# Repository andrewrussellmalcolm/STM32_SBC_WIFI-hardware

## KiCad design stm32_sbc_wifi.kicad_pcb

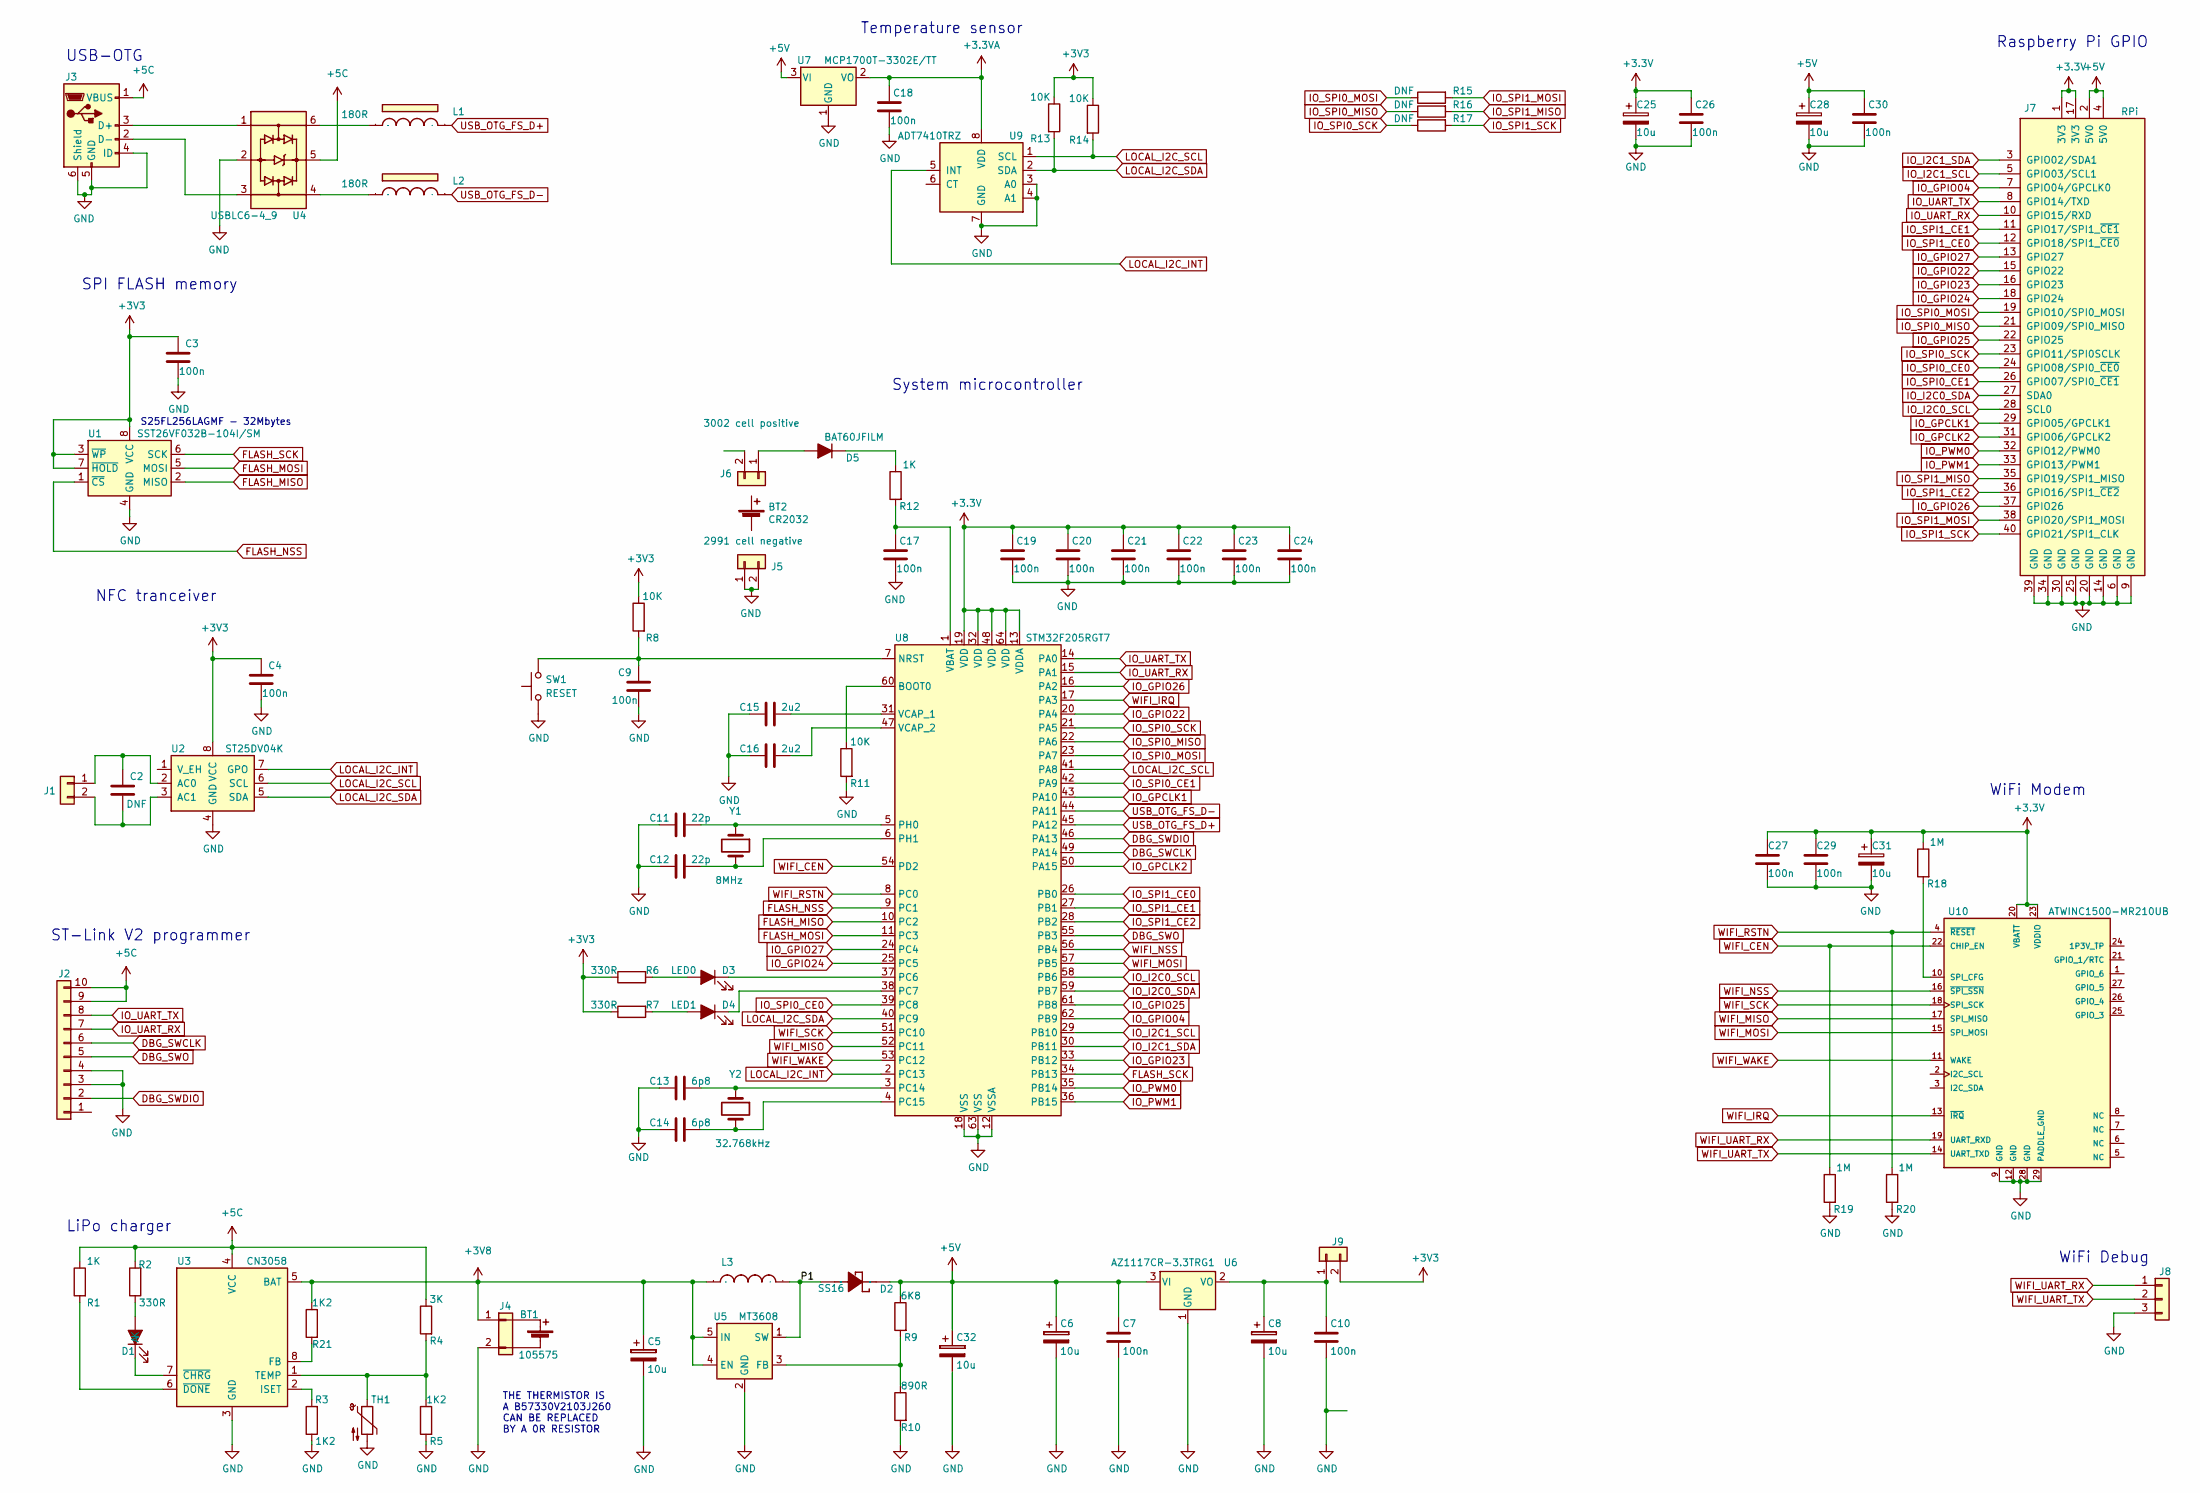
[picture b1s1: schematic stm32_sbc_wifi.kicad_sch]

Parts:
BT1: 105575; 103040_5000mAh_LiPo; Voltage 3; PartNo 97384022
BT2: CR2032; dummy
C2: DNF; C_0603_1608Metric
C3, C7, C9, C10, C17, C19, C20, C21, C22, C23, C24, C26, C30: 100n; C_0603_1608Metric; PartNo C0603C104K3RACTU
C4, C18: 100n; C_0603_1608Metric; Voltage 50V; PartNo C0603C104K4RACTU
C5, C6, C8, C32: 10u; CP_EIA-3216-10_Kemet-I; PartNo TAJR106K006RNJ
C11, C12: 22p; C_0603_1608Metric; PartNo C0603C220J5GACTU
C13, C14: 6p8; C_0603_1608Metric; PartNo C0603C689C5GACTU
C15, C16: 2u2; C_0603_1608Metric; PartNo C0603C225K4PACTU
C25, C28: 10u; CP_EIA-3216-10_Kemet-I
C27, C29: 100n; C_0603_1608Metric; Voltage 50V; PartNo C0603C104K3RACTU
C31: 10u; CP_EIA-3216-10_Kemet-I; Voltage 6.3V; PartNo TAJR106K006RNJ
D1: LTST-C190KRKT; 3mm_right_angle_LED
D2: SS16; SM_DIODE_DO214AC_1; PartNo SS16
D3: LED0; 3mm_right_angle_LED; PartNo LS Q976
D4: LED1; 3mm_right_angle_LED; PartNo LB Q39E-L2OO-35-1
D5: BAT60JFILM; D_SOD-323; PartNo BAT60JFILM
J1: Conn_01x02; Molex_PicoBlade_53047-0210_1x02_P1.25mm_Vertical; PartNo 53047-0210
J2: Conn_01x10; IDC-Header_2x05_P2.54mm_Vertical; PartNo T821110A1S100CEU
J3: USB_OTG; USB_Micro-B_Molex-105017-0001; PartNo 105017-0001
J4: Conn_01x02; JST_PH_B2B-PH-K_1x02_P2.00mm_Vertical
J5: 2991 cell negative; SM_BATTERY_2991_(KEYSTONE)_1; PartNo 2991TR
J6: 3002 cell positive; SM_BATTERY_3002_(KEYSTONE)_1; PartNo 3002TR
J7: RPi; PinHeader_2x20_P2.54mm_Vertical
J8: Conn_01x03; Molex_KK-254_AE-6410-03A_1x03_P2.54mm_Vertical; PartNo 22-27-2031
J9: Conn_01x02; PinHeader_1x02_P2.54mm_Horizontal
L1, L2: 180R; L_0603_1608Metric; PartNo 742792624
L3: L_10.4x10.4_H4.8; PartNo SRN5020-150M; Farnell not FEC, RS 749-8653
R1, R12: 1K; R_0603_1608Metric; PartNo CRG0603F1K
R2: 330R; R_0603_1608Metric
R3: 1K2; R_0603_1608Metric
R4: 3K; R_0603_1608Metric; PartNo CRG0603F1K
R5, R21: 1K2; R_0603_1608Metric; PartNo CRG0603F1K
R6, R7: 330R; R_0603_1608Metric; PartNo CRG0603F330R
R8, R11: 10K; R_0603_1608Metric; PartNo CRG0603F10K
R9: 6K8; R_0603_1608Metric; PartNo CRG0603F1K
R10: 890R; R_0603_1608Metric; PartNo CRG0603F1K
R13, R14: 10K; R_0603_1608Metric; PartNo CRG0603F2K2
R15, R16, R17: DNF; R_0603_1608Metric; PartNo CRG0603F330R
R18, R19, R20: 1M; R_0603_1608Metric; PartNo CRG0603F10K
SW1: RESET; SW_SPST_B3S-1000
TH1: B57330V2103J260; R_0603_1608Metric
U1: SST26VF032B-104I/SM; SOIC-8W_5.3x5.3mm_P1.27mm; PartNo SST26VF032B-104I/SM
U2: ST25DV04K; SOIC-8_3.9x4.9mm_P1.27mm; PartNo ST25DV04K
U3: CN3058; SOIC-8-1EP_3.9x4.9mm_P1.27mm_EP2.29x3mm
U4: USBLC6-4_9; SOT-23-6; PartNo USBLC6-2SC6Y
U5: MT3608; SOT-23-6
U6: AZ1117CR-3.3TRG1; SOT-89-3; PartNo AZ1117CR-3.3TRG1
U7: MCP1700T-3302E/TT; SOT-23
U8: STM32F205RGT7; LQFP-64_10x10mm_P0.5mm; PartNo STM32F205RGT7
U9: ADT7410TRZ; SOIC-8_3.9x4.9mm_P1.27mm; PartNo HTS221TR
U10: ATWINC1500-MR210UB; MICROCHIP_ATWINC1500-MR210UB
Y1: 8MHz; Crystal_SMD_5032-2Pin_5.0x3.2mm; PartNo 144-5033
Y2: 32.768kHz; Crystal_SMD_2012-2Pin_2.0x1.2mm; PartNo 144-2324

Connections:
+3.3VA: C18.2, U7.2 (VO), U9.8 (VDD)
+3V8: C5.1, J4.1, L3.1, R21.1, U3.5 (BAT), U5.4 (EN), U5.5 (IN)
+5C: J2.9, J2.10, J3.1 (VBUS), R1.1, R2.2, R4.1, U3.4 (VCC), U4.5
+5V: C6.1, C7.1, C28.1, C30.2, C32.1, D2.1 (ANODE), J7.2 (5V0), J7.4 (5V0), R9.1, U6.3 (VI), U7.3 (VI)
/P1: D2.2 (CATHODE), L3.2, U5.1 (SW)
DBG_SWCLK: J2.6, U8.49 (PA14)
DBG_SWDIO: J2.2, U8.46 (PA13)
DBG_SWO: J2.5, U8.55 (PB3)
FLASH_MISO: U1.2 (MISO), U8.10 (PC2)
FLASH_MOSI: U1.5 (MOSI), U8.11 (PC3)
FLASH_NSS: U1.1 (~CS), U8.9 (PC1)
FLASH_SCK: U1.6 (SCK), U8.34 (PB13)
GND: C3.1, C4.1, C5.2, C6.2, C7.2, C8.2, C9.1, C10.2, C11.2, C12.2, C13.2, C14.2, C15.2, C16.2, C17.1, C18.1, C19.1, C20.1, C21.1, C22.1, C23.1, C24.1, C25.2, C26.1, C27.2, C28.2, C29.2, C30.1, C31.2, C32.2, J2.3, J2.4, J3.4 (ID), J3.5 (GND), J3.6 (Shield), J4.2, J5.1, J5.2, J7.6 (GND), J7.9 (GND), J7.14 (GND), J7.20 (GND), J7.25 (GND), J7.30 (GND), J7.34 (GND), J7.39 (GND), J8.3, R3.1, R5.2, R10.2, R11.2, R19.2, R20.2, SW1.1, TH1.2, U1.4 (GND), U2.4 (GND), U3.3 (GND), U4.2, U5.2 (GND), U6.1 (GND), U7.1 (GND), U8.12 (VSSA), U8.18 (VSS), U8.63 (VSS), U9.3 (A0), U9.4 (A1), U9.7 (GND), U10.9 (GND), U10.12 (GND), U10.28 (GND), U10.29 (PADDLE_GND)
IO_GPCLK1: J7.29 (GPIO05/GPCLK1), U8.43 (PA10)
IO_GPCLK2: J7.31 (GPIO06/GPCLK2), U8.50 (PA15)
IO_GPIO04: J7.7 (GPIO04/GPCLK0), U8.62 (PB9)
IO_GPIO22: J7.15 (GPIO22), U8.20 (PA4)
IO_GPIO23: J7.16 (GPIO23), U8.33 (PB12)
IO_GPIO24: J7.18 (GPIO24), U8.25 (PC5)
IO_GPIO25: J7.22 (GPIO25), U8.61 (PB8)
IO_GPIO26: J7.37 (GPIO26), U8.16 (PA2)
IO_GPIO27: J7.13 (GPIO27), U8.24 (PC4)
IO_I2C0_SCL: J7.28 (SCL0), U8.58 (PB6)
IO_I2C0_SDA: J7.27 (SDA0), U8.59 (PB7)
IO_I2C1_SCL: J7.5 (GPIO03/SCL1), U8.29 (PB10)
IO_I2C1_SDA: J7.3 (GPIO02/SDA1), U8.30 (PB11)
IO_PWM0: J7.32 (GPIO12/PWM0), U8.35 (PB14)
IO_PWM1: J7.33 (GPIO13/PWM1), U8.36 (PB15)
IO_SPI0_CE0: J7.24 (GPIO08/SPI0_~CE0), U8.39 (PC8)
IO_SPI0_CE1: J7.26 (GPIO07/SPI0_~CE1), U8.42 (PA9)
IO_SPI0_MISO: J7.21 (GPIO09/SPI0_MISO), R16.1, U8.22 (PA6)
IO_SPI0_MOSI: J7.19 (GPIO10/SPI0_MOSI), R15.1, U8.23 (PA7)
IO_SPI0_SCK: J7.23 (GPIO11/SPI0SCLK), R17.1, U8.21 (PA5)
IO_SPI1_CE0: J7.12 (GPIO18/SPI1_~CE0), U8.26 (PB0)
IO_SPI1_CE1: J7.11 (GPIO17/SPI1_~CE1), U8.27 (PB1)
IO_SPI1_CE2: J7.36 (GPIO16/SPI1_~CE2), U8.28 (PB2)
IO_SPI1_MISO: J7.35 (GPIO19/SPI1_MISO), R16.2
IO_SPI1_MOSI: J7.38 (GPIO20/SPI1_MOSI), R15.2
IO_SPI1_SCK: J7.40 (GPIO21/SPI1_CLK), R17.2
IO_UART_RX: J2.7, J7.10 (GPIO15/RXD), U8.15 (PA1)
IO_UART_TX: J2.8, J7.8 (GPIO14/TXD), U8.14 (PA0)
LOCAL_I2C_INT: U2.7 (GPO), U8.2 (PC13), U9.5 (INT)
LOCAL_I2C_SCL: R14.2, U2.6 (SCL), U8.41 (PA8), U9.1 (SCL)
LOCAL_I2C_SDA: R13.2, U2.5 (SDA), U8.40 (PC9), U9.2 (SDA)
unnamed: D1.2 (A), R2.1
unnamed: D1.1 (K), U3.7 (~CHRG)
unnamed: D3.2 (A), R6.2
unnamed: D3.1 (K), U8.37 (PC6)
unnamed: D4.2 (A), R7.2
unnamed: D4.1 (K), U8.38 (PC7)
unnamed: D5.2 (A), J6.1
unnamed: D5.1 (K), R12.1
unnamed: C2.2, J1.1, U2.2 (AC0)
unnamed: C2.1, J1.2, U2.3 (AC1)
unnamed: J3.3 (D+), U4.1
unnamed: J3.2 (D-), U4.3
unnamed: C8.1, C10.1, J9.1, U6.2 (VO)
unnamed: L1.1, U4.6
unnamed: L2.1, U4.4
unnamed: R21.2, U3.8 (FB)
unnamed: R3.2, U3.2 (ISET)
unnamed: R4.2, R5.1, TH1.1, U3.1 (TEMP)
unnamed: R1.2, U3.6 (~DONE)
unnamed: R9.2, R10.1, U5.3 (FB)
unnamed: R11.1, U8.60 (BOOT0)
unnamed: C9.2, R8.2, SW1.2, U8.7 (NRST)
unnamed: C13.1, U8.3 (PC14), Y2.1
unnamed: C14.1, U8.4 (PC15), Y2.2
unnamed: C11.1, U8.5 (PH0), Y1.1
unnamed: C12.1, U8.6 (PH1), Y1.2
unnamed: C17.2, R12.2, U8.1 (VBAT)
unnamed: C15.1, U8.31 (VCAP_1)
unnamed: C16.1, U8.47 (VCAP_2)
unnamed: R18.2, U10.10 (SPI_CFG)
USB_OTG_FS_D+: L1.2, U8.45 (PA12)
USB_OTG_FS_D-: L2.2, U8.44 (PA11)
WIFI_CEN: R19.1, U8.54 (PD2), U10.22 (CHIP_EN)
WIFI_IRQ: U8.17 (PA3), U10.13 (~IRQ)
WIFI_MISO: U8.52 (PC11), U10.17 (SPI_MISO)
WIFI_MOSI: U8.57 (PB5), U10.15 (SPI_MOSI)
WIFI_NSS: U8.56 (PB4), U10.16 (~SPI_SSN)
WIFI_RSTN: R20.1, U8.8 (PC0), U10.4 (~RESET)
WIFI_SCK: U8.51 (PC10), U10.18 (SPI_SCK)
WIFI_UART_RX: J8.1, U10.19 (UART_RXD)
WIFI_UART_TX: J8.2, U10.14 (UART_TXD)
WIFI_WAKE: U8.53 (PC12), U10.11 (WAKE)

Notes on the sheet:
LiPo charger
Raspberry Pi GPIO
SPI FLASH memory
WiFi Debug
S25FL256LAGMF - 32Mbytes
THE THERMISTOR IS A B57330V2103J260 CAN BE REPLACED BY A 0R RESISTOR
NFC tranceiver
USB-OTG
System microcontroller
WiFi Modem
ST-Link V2 programmer
Temperature sensor

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
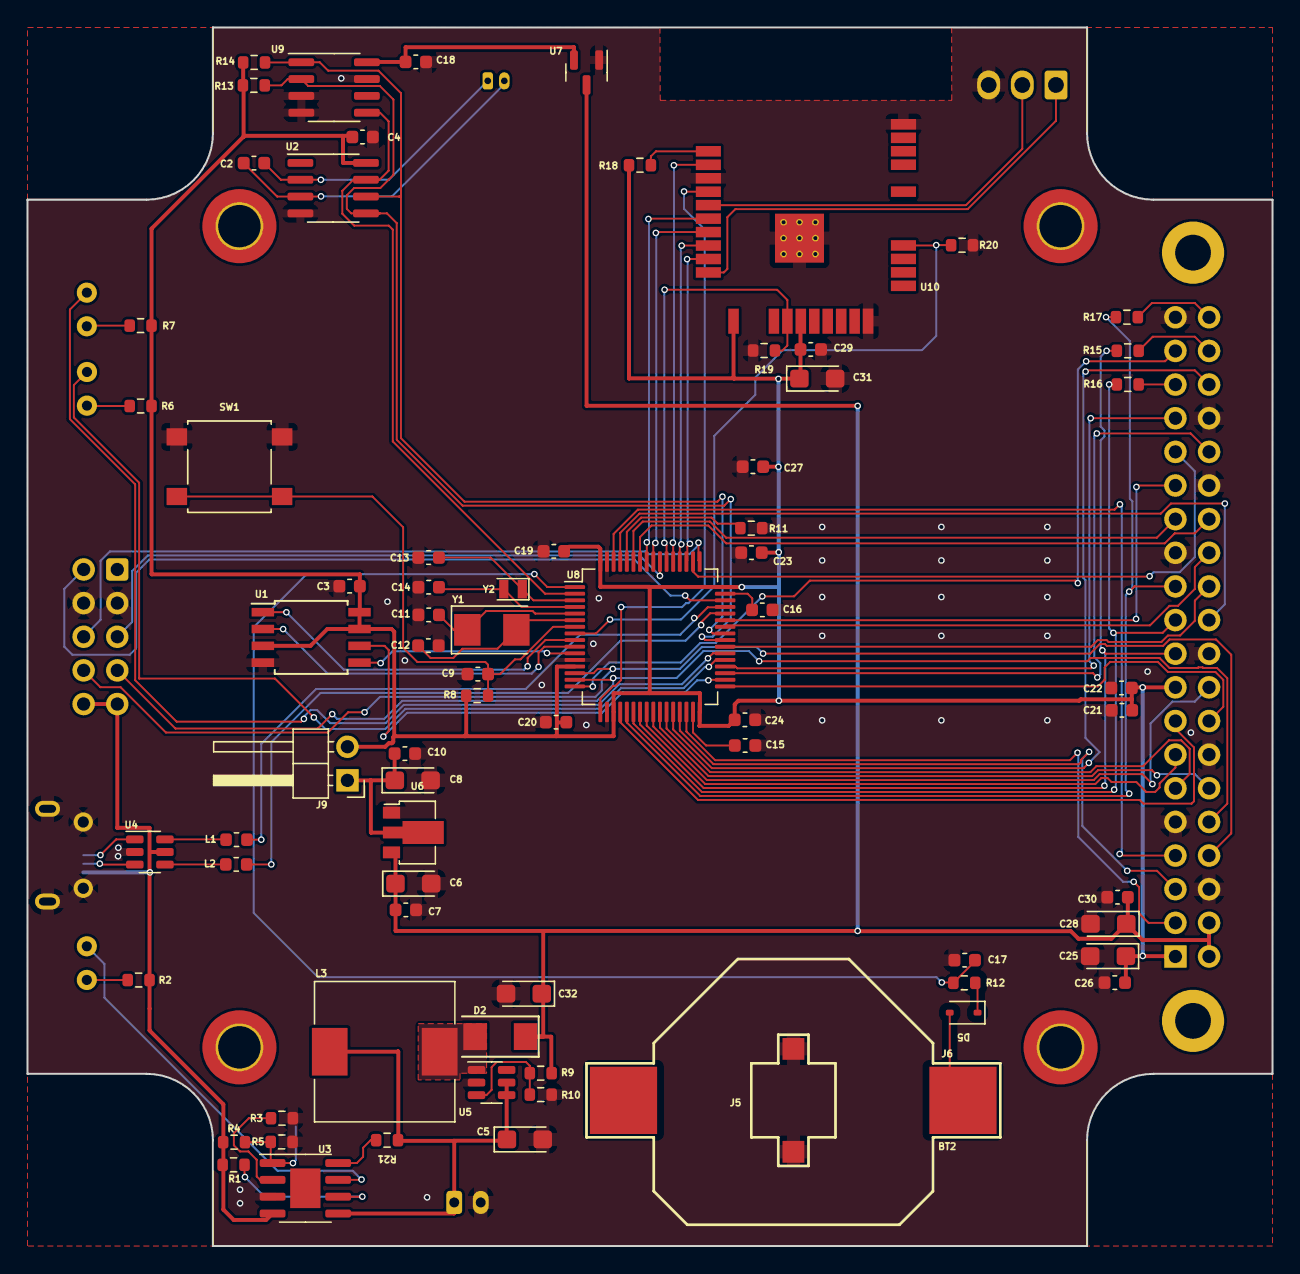
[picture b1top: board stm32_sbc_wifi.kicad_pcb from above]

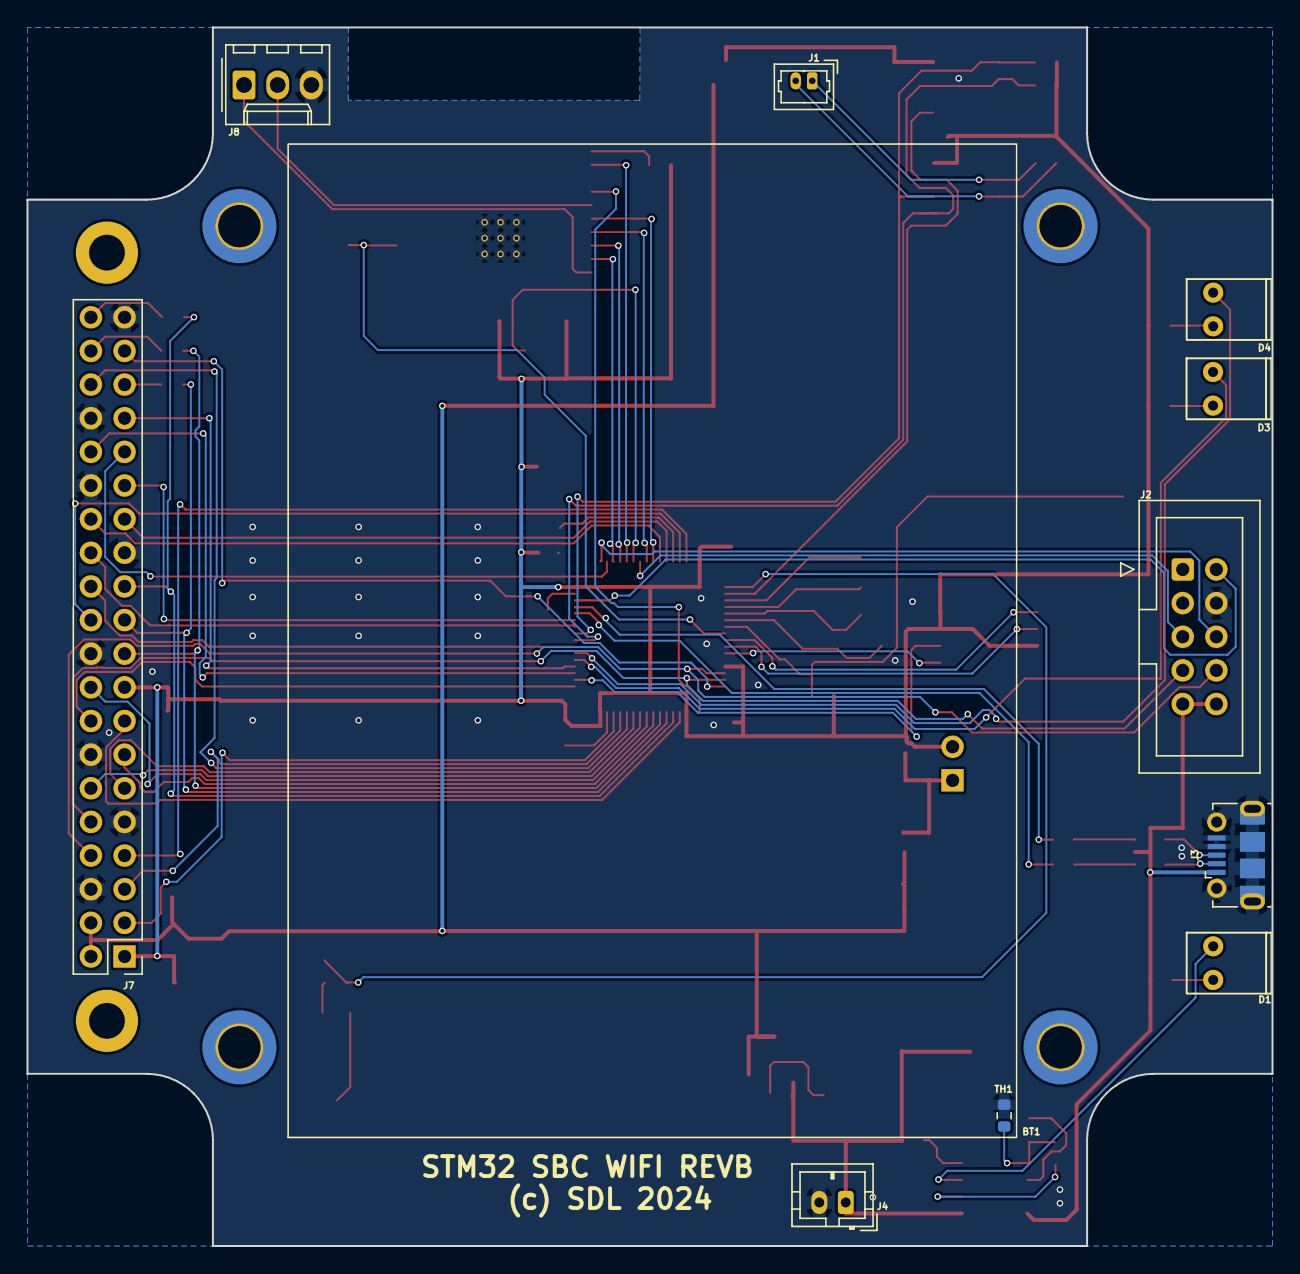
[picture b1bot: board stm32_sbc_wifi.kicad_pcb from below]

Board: 2 copper layers, 94.0 x 92.0 mm, 87 parts (11 on the bottom side), 87 nets.

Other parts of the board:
locked: MountingHole_2.7mm_M2.5_DIN965_Pad
locked#2: MountingHole_2.7mm_M2.5_DIN965_Pad

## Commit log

2024-07-03 added files
